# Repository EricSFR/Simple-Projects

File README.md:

# Simple-Projects
In this repository i'll show some of my projects, manly for the ubniversity

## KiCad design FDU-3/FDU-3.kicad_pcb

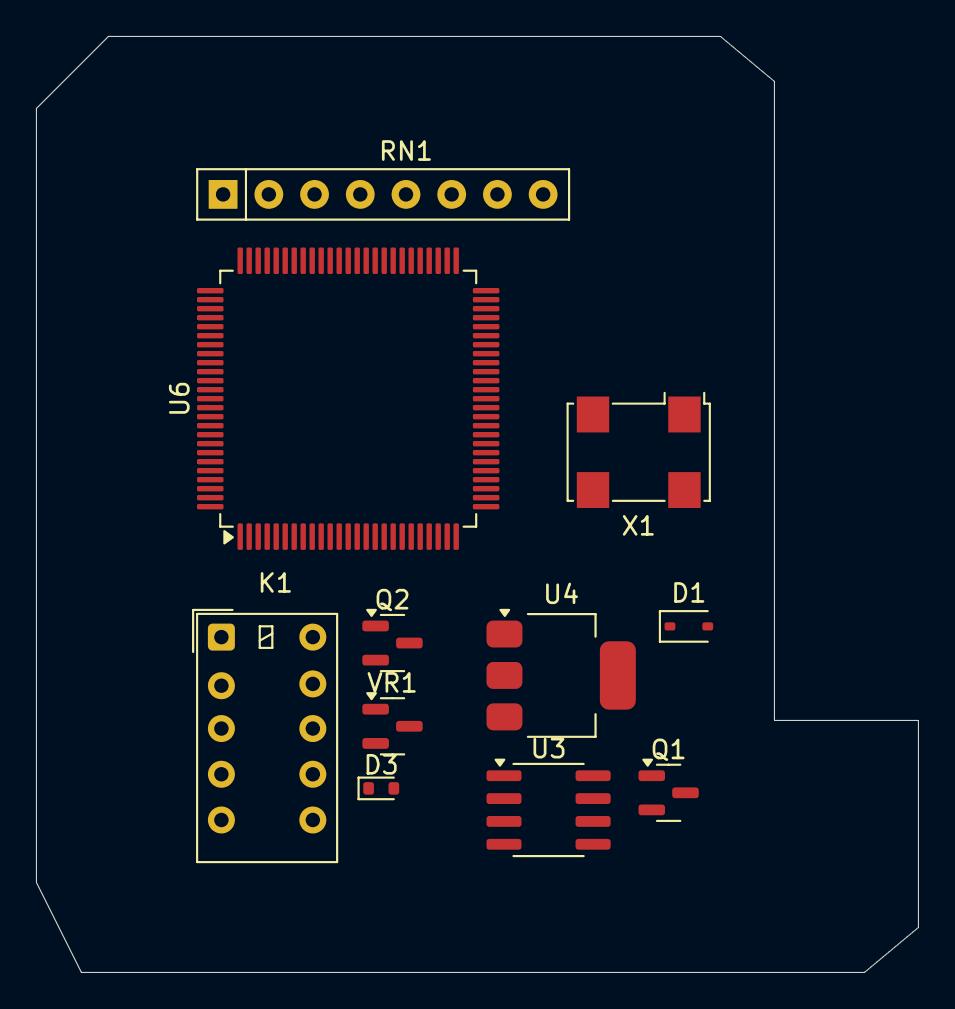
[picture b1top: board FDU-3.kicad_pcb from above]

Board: 2 copper layers, 49.0 x 52.0 mm, 11 parts (0 on the bottom side), 10 nets, no tracks yet.

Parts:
D1: ?; D_SOD-323
D3: 1N4148WT; D_SOD-523
K1: ATQ209; Relay_DPDT_Kemet_EC2
Q1: BC807; SOT-23
Q2: MMBF170; SOT-23
RN1: 10k; R_Array_SIP8
U3: LM2672M-5.0; SOIC-8_3.9x4.9mm_P1.27mm
U4: LM2937xMP; SOT-223-3_TabPin2
U6: CY7C67300-100AX; TQFP-100_14x14mm_P0.5mm
VR1: BZX84Cxx; SOT-23
X1: CFPS-72; Oscillator_SMD_IQD_IQXO70-4Pin_7.5x5.0mm

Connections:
+3V3: RN1.4 (R2.2), U4.3 (VO), X1.4 (+Vs)
+5V: D1.1 (K), D3.1 (K), K1.1, U3.4 (FB), U3.8 (VSW), U4.1 (VI)
/CONECTORES/D1+: K1.4, U6.22 (DM1A)
/CONECTORES/RELÉ: Q2.1 (G), U6.53 (PWM2/RTS/A2/GPIO18)
GND: D1.2 (A), U3.6 (GND), U4.2 (GND), U6.6 (AGND), U6.15 (BOOSTGND), U6.26 (GND), U6.51 (GND), U6.75 (GND), U6.100 (GND), X1.2 (GND)
unnamed: D3.2 (A), K1.10, Q2.3 (D)
unnamed: RN1.3 (R2.1), X1.1 (EN)
unnamed: U6.16 (BOOSTVcc), U6.21 (AVcc), U6.37 (VCC), U6.63 (VCC), U6.88 (VCC)
unnamed: U6.29 (XTALIN), X1.3 (Output)
unnamed: K1.8, VR1.3 (K)

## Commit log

2024-04-22 A 555 based wave generator
2024-04-28 Rename WaveGenerator2.PDF to FunctionGenBotCopper.PDF
2024-04-28 Rename image.png to 3dImage.png
2024-04-28 Rename WaveGenerator2.pdsprj to ProteusFile.pdsprj
